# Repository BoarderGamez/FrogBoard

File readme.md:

# FrogBoard
My own devboard, from keyboard, to devboard 👍

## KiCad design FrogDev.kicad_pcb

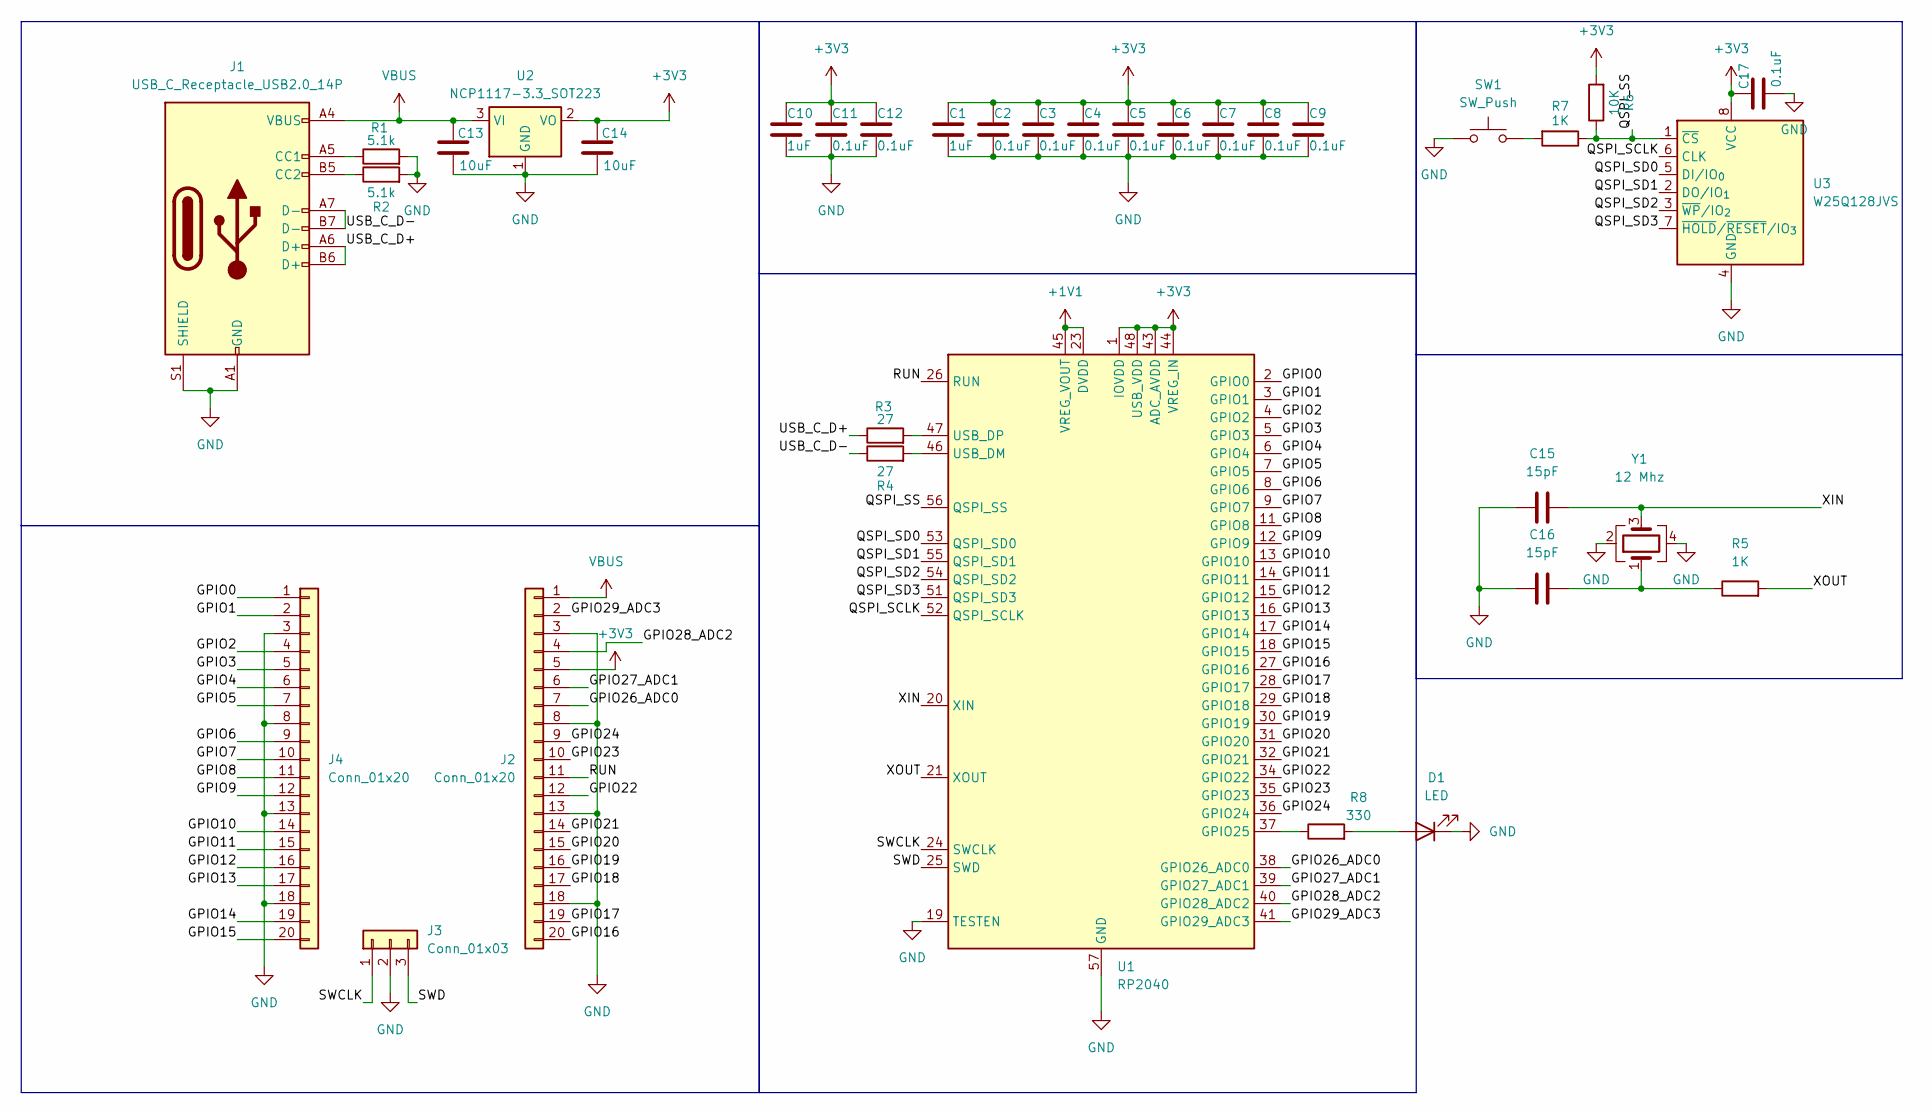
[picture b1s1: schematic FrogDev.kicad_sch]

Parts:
C1, C10: 1uF; C_0402_1005Metric
C2, C3, C4, C5, C6, C7, C8, C9, C11, C12, C17: 0.1uF; C_0402_1005Metric
C13, C14: 10uF; C_0402_1005Metric
C15, C16: 15pF; C_0402_1005Metric
D1: LED; LED_0603_1608Metric
J1: USB_C_Receptacle_USB2.0_14P; USB_C_Receptacle_HRO_TYPE-C-31-M-12
J2, J4: Conn_01x20; PinHeader_1x20_P2.54mm_Vertical
J3: Conn_01x03; PinHeader_1x03_P2.54mm_Vertical
R1, R2: 5.1k; R_0402_1005Metric
R3, R4: 27; R_0402_1005Metric
R5, R7: 1K; R_0402_1005Metric
R6: 10K; R_0402_1005Metric
R8: 330; R_0402_1005Metric
SW1: SW_Push; SW_Push_SPST_NO_Alps_SKRK
U1: RP2040; QFN-56-1EP_7x7mm_P0.4mm_EP3.2x3.2mm
U2: NCP1117-3.3_SOT223; SOT-223-3_TabPin2
U3: W25Q128JVS; SOIC-8_5.3x5.3mm_P1.27mm
Y1: 12 Mhz; Crystal_SMD_3225-4Pin_3.2x2.5mm

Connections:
+1V1: U1.23 (DVDD), U1.45 (VREG_VOUT), U1.50 (DVDD)
+3V3: C1.1, C2.1, C3.1, C4.1, C5.1, C6.1, C7.1, C8.1, C9.1, C10.1, C11.1, C12.1, C14.1, C17.1, J2.5, R6.2, U1.1 (IOVDD), U1.10 (IOVDD), U1.22 (IOVDD), U1.33 (IOVDD), U1.42 (IOVDD), U1.43 (ADC_AVDD), U1.44 (VREG_IN), U1.48 (USB_VDD), U1.49 (IOVDD), U2.2 (VO), U3.8 (VCC)
/GPIO0: J4.1, U1.2 (GPIO0)
/GPIO1: J4.2, U1.3 (GPIO1)
/GPIO2: J4.4, U1.4 (GPIO2)
/GPIO3: J4.5, U1.5 (GPIO3)
/GPIO4: J4.6, U1.6 (GPIO4)
/GPIO5: J4.7, U1.7 (GPIO5)
/GPIO6: J4.9, U1.8 (GPIO6)
/GPIO7: J4.10, U1.9 (GPIO7)
/GPIO8: J4.11, U1.11 (GPIO8)
/GPIO9: J4.12, U1.12 (GPIO9)
/GPIO10: J4.14, U1.13 (GPIO10)
/GPIO11: J4.15, U1.14 (GPIO11)
/GPIO12: J4.16, U1.15 (GPIO12)
/GPIO13: J4.17, U1.16 (GPIO13)
/GPIO14: J4.19, U1.17 (GPIO14)
/GPIO15: J4.20, U1.18 (GPIO15)
/GPIO16: J2.20, U1.27 (GPIO16)
/GPIO17: J2.19, U1.28 (GPIO17)
/GPIO18: J2.17, U1.29 (GPIO18)
/GPIO19: J2.16, U1.30 (GPIO19)
/GPIO20: J2.15, U1.31 (GPIO20)
/GPIO21: J2.14, U1.32 (GPIO21)
/GPIO22: J2.12, U1.34 (GPIO22)
/GPIO23: J2.10, U1.35 (GPIO23)
/GPIO24: J2.9, U1.36 (GPIO24)
/GPIO26_ADC0: J2.7, U1.38 (GPIO26_ADC0)
/GPIO27_ADC1: J2.6, U1.39 (GPIO27_ADC1)
/GPIO28_ADC2: J2.4, U1.40 (GPIO28_ADC2)
/GPIO29_ADC3: J2.2, U1.41 (GPIO29_ADC3)
/QSPI_SCLK: U1.52 (QSPI_SCLK), U3.6 (CLK)
/QSPI_SD0: U1.53 (QSPI_SD0), U3.5 (DI/IO_{0})
/QSPI_SD1: U1.55 (QSPI_SD1), U3.2 (DO/IO_{1})
/QSPI_SD2: U1.54 (QSPI_SD2), U3.3 (~WP/IO_{2})
/QSPI_SD3: U1.51 (QSPI_SD3), U3.7 (~HOLD/~RESET/IO_{3})
/QSPI_SS: R6.1, R7.1, U1.56 (QSPI_SS), U3.1 (~CS)
/RUN: J2.11, U1.26 (RUN)
/SWCLK: J3.1, U1.24 (SWCLK)
/SWD: J3.3, U1.25 (SWD)
/USB_C_D+: J1.A6 (D+), J1.B6 (D+), R3.1
/USB_C_D-: J1.A7 (D-), J1.B7 (D-), R4.1
/XIN: C15.2, U1.20 (XIN), Y1.3
/XOUT: R5.2, U1.21 (XOUT)
GND: C1.2, C2.2, C3.2, C4.2, C5.2, C6.2, C7.2, C8.2, C9.2, C10.2, C11.2, C12.2, C13.2, C14.2, C15.1, C16.1, C17.2, D1.1 (K), J1.A1 (GND), J1.A12 (GND), J1.B1 (GND), J1.B12 (GND), J1.S1 (SHIELD), J2.3, J2.8, J2.13, J2.18, J3.2, J4.3, J4.8, J4.13, J4.18, R1.2, R2.2, SW1.1, U1.19 (TESTEN), U1.57 (GND), U2.1 (GND), U3.4 (GND), Y1.2, Y1.4
unnamed: C16.2, R5.1, Y1.1
unnamed: D1.2 (A), R8.2
unnamed: J1.A5 (CC1), R1.1
unnamed: J1.B5 (CC2), R2.1
unnamed: R7.2, SW1.2
unnamed: R8.1, U1.37 (GPIO25)
unnamed: R4.2, U1.46 (USB_DM)
unnamed: R3.2, U1.47 (USB_DP)
VBUS: C13.1, J1.A4 (VBUS), J1.A9 (VBUS), J1.B4 (VBUS), J1.B9 (VBUS), J2.1, U2.3 (VI)

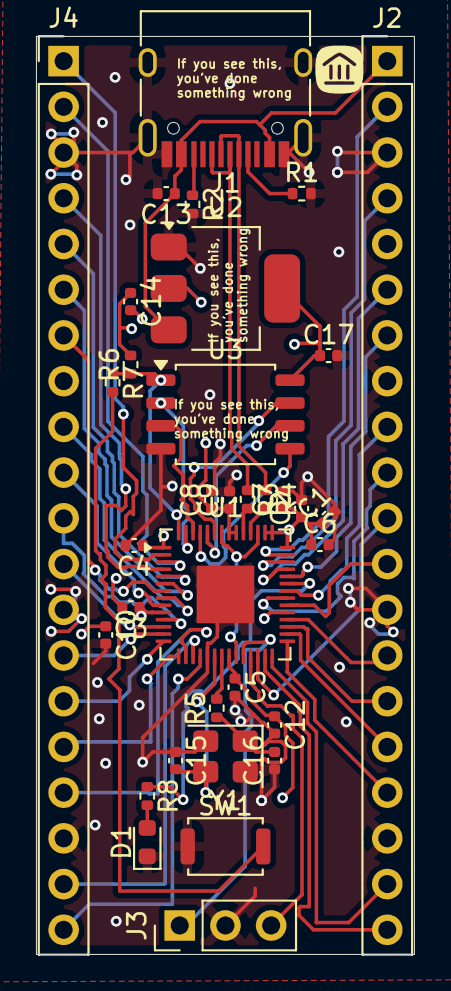
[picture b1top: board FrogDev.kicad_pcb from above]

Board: 4 copper layers, 21.0 x 51.0 mm, 34 parts (0 on the bottom side), 54 nets.

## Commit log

2025-12-14 Create temp
2025-12-14 Update BOM with new entries and corrections
2025-12-15 Revise BOM entries and fix formatting issues
    Updated the BOM file by replacing the old entries with new ones and correcting formatting issues.
